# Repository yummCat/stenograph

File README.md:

# stenograph

Do you ever feel like Edward Scissorhands? With dainty, Paganini-like fingers that you know have the power to move the world with every word flowing from your fingertips? Do you feel as though you can never stop the outpouring of verse, and thus feel the need to procure a suitable speed-typing device to help you spill it all onto paper? Well, do I have good news for you!

We decided to make a heart-shaped stenograph. Now, each chord—every word—will will ring as vibrantly as a guitar with our custom-designed, heart-shaped case. Suitable for writing long letters to your loved ones, or cringey—nay, impassioned—poetry for your unsuspecting crush, the Heartograph is the solution for you!

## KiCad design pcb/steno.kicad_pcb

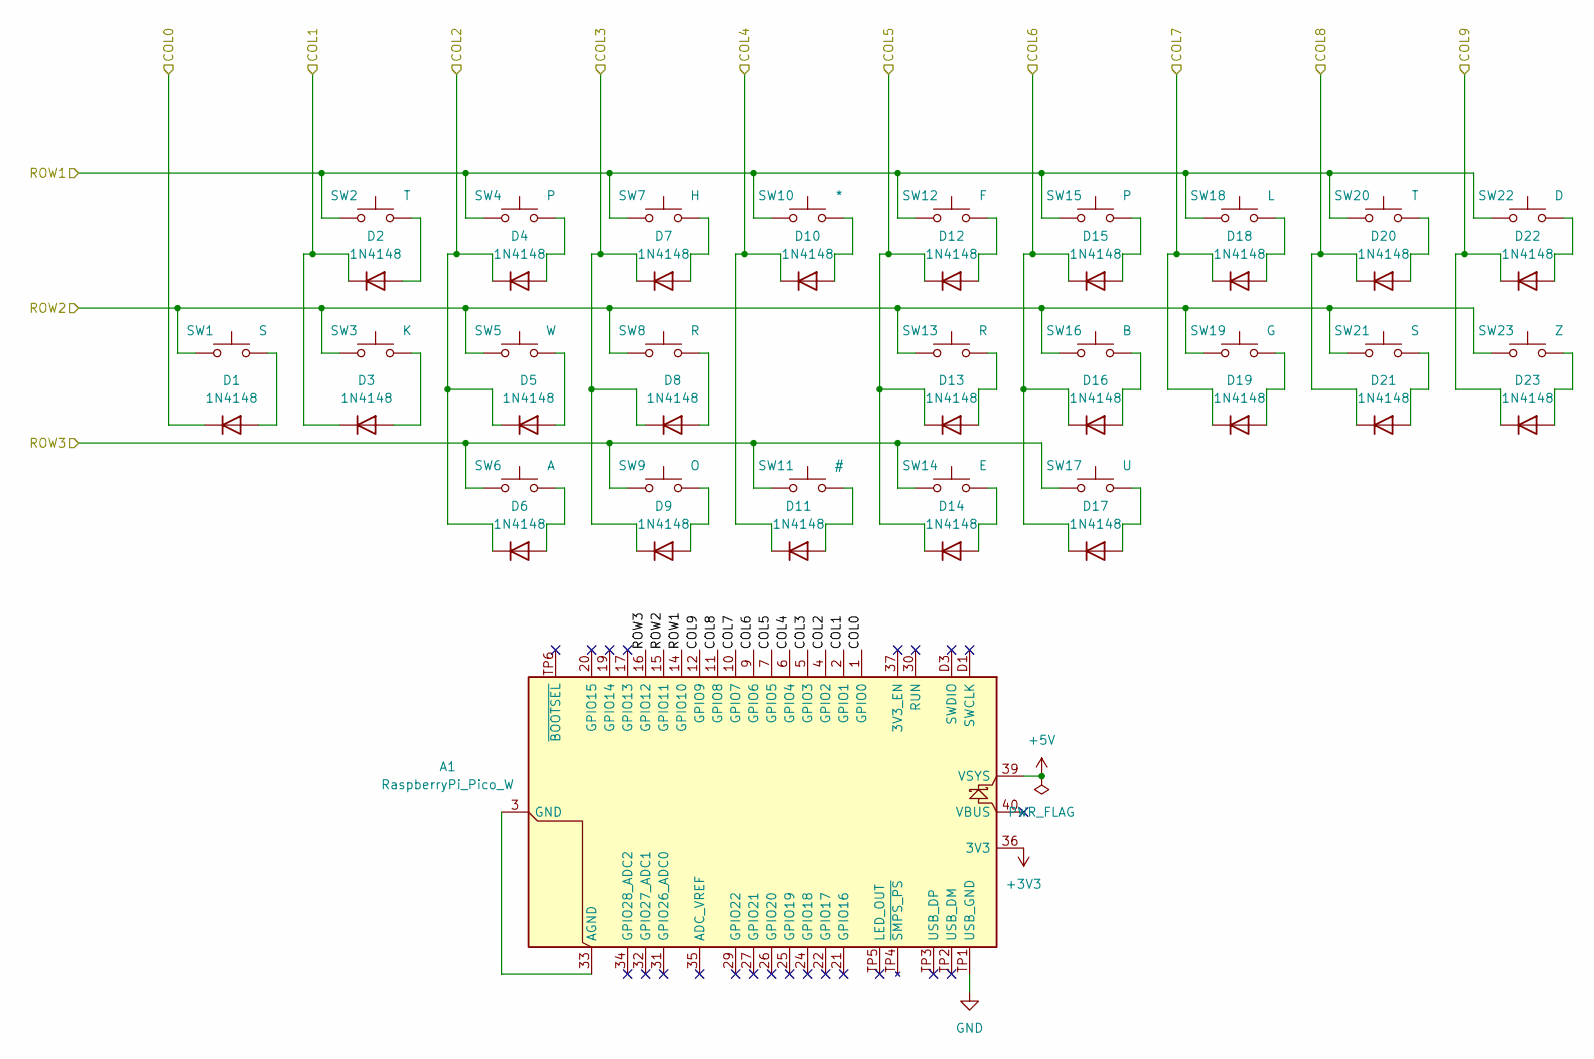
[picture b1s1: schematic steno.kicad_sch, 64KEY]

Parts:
A1: RaspberryPi_Pico_W; RaspberryPi_Pico_W_SMD1
D1, D2, D3, D4, D5, D6, D7, D8, D9, D10, D11, D12, D13, D14, D15, D16, D17, D18, D19, D20, D21, D22, D23: 1N4148; D_DO-35_SOD27_P7.62mm_Horizontal
SW1: S; SW_Cherry_MX_2.25u_PCB
SW2, SW20: T; SW_Cherry_MX_1.00u_PCB
SW3: K; SW_Cherry_MX_1.00u_PCB
SW4, SW15: P; SW_Cherry_MX_1.00u_PCB
SW5: W; SW_Cherry_MX_1.00u_PCB
SW6: A; SW_Cherry_MX_1.00u_PCB
SW7: H; SW_Cherry_MX_1.00u_PCB
SW8, SW13: R; SW_Cherry_MX_1.00u_PCB
SW9: O; SW_Cherry_MX_1.00u_PCB
SW10: *; SW_Cherry_MX_2.25u_PCB
SW11: #; SW_Cherry_MX_1.00u_PCB
SW12: F; SW_Cherry_MX_1.00u_PCB
SW14: E; SW_Cherry_MX_1.00u_PCB
SW16: B; SW_Cherry_MX_1.00u_PCB
SW17: U; SW_Cherry_MX_1.00u_PCB
SW18: L; SW_Cherry_MX_1.00u_PCB
SW19: G; SW_Cherry_MX_1.00u_PCB
SW21: S; SW_Cherry_MX_1.00u_PCB
SW22: D; SW_Cherry_MX_1.00u_PCB
SW23: Z; SW_Cherry_MX_1.00u_PCB

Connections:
+3V3: A1.36 (3V3)
+5V: A1.39 (VSYS)
/COL0: A1.1 (GPIO0), D1.1 (K)
/COL1: A1.2 (GPIO1), D2.1 (K), D3.1 (K)
/COL2: A1.4 (GPIO2), D4.1 (K), D5.1 (K), D6.1 (K)
/COL3: A1.5 (GPIO3), D7.1 (K), D8.1 (K), D9.1 (K)
/COL4: A1.6 (GPIO4), D10.1 (K), D11.1 (K)
/COL5: A1.7 (GPIO5), D12.1 (K), D13.1 (K), D14.1 (K)
/COL6: A1.9 (GPIO6), D15.1 (K), D16.1 (K), D17.1 (K)
/COL7: A1.10 (GPIO7), D18.1 (K), D19.1 (K)
/COL8: A1.11 (GPIO8), D20.1 (K), D21.1 (K)
/COL9: A1.12 (GPIO9), D22.1 (K), D23.1 (K)
/ROW1: A1.14 (GPIO10), SW2.1, SW4.1, SW7.1, SW10.1, SW12.1, SW15.1, SW18.1, SW20.1, SW22.1
/ROW2: A1.15 (GPIO11), SW1.1, SW3.1, SW5.1, SW8.1, SW13.1, SW16.1, SW19.1, SW21.1, SW23.1
/ROW3: A1.16 (GPIO12), SW6.1, SW9.1, SW11.1, SW14.1, SW17.1
GND: A1.TP1 (USB_GND)
unnamed: A1.3 (GND), A1.8 (GND), A1.13 (GND), A1.18 (GND), A1.23 (GND), A1.28 (GND), A1.33 (AGND), A1.38 (GND), A1.D2 (GND)
unnamed: D1.2 (A), SW1.2
unnamed: D2.2 (A), SW2.2
unnamed: D3.2 (A), SW3.2
unnamed: D4.2 (A), SW4.2
unnamed: D5.2 (A), SW5.2
unnamed: D6.2 (A), SW6.2
unnamed: D7.2 (A), SW7.2
unnamed: D8.2 (A), SW8.2
unnamed: D9.2 (A), SW9.2
unnamed: D10.2 (A), SW10.2
unnamed: D11.2 (A), SW11.2
unnamed: D12.2 (A), SW12.2
unnamed: D13.2 (A), SW13.2
unnamed: D14.2 (A), SW14.2
unnamed: D15.2 (A), SW15.2
unnamed: D16.2 (A), SW16.2
unnamed: D17.2 (A), SW17.2
unnamed: D18.2 (A), SW18.2
unnamed: D19.2 (A), SW19.2
unnamed: D20.2 (A), SW20.2
unnamed: D21.2 (A), SW21.2
unnamed: D22.2 (A), SW22.2
unnamed: D23.2 (A), SW23.2

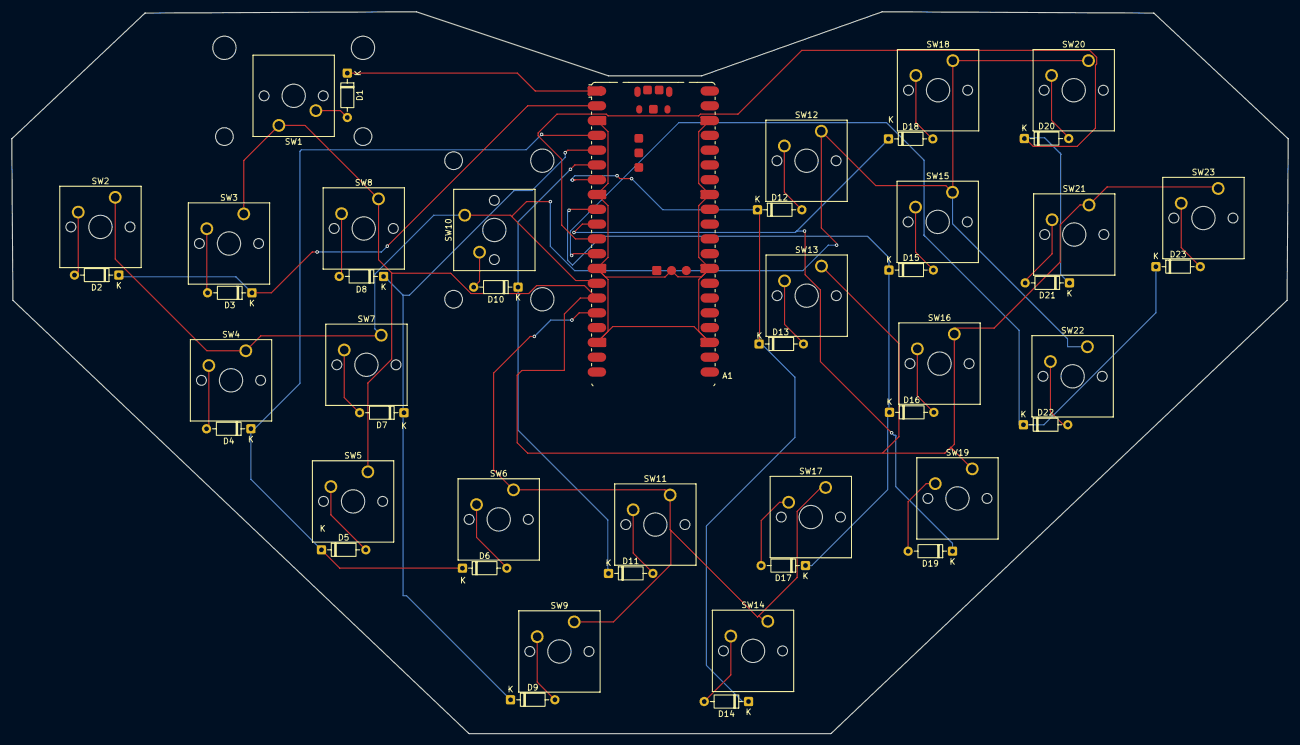
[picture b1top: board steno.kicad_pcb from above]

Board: 2 copper layers, 219.2 x 124.0 mm, 47 parts (0 on the bottom side), 37 nets.

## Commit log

2025-07-04 added files to folders
